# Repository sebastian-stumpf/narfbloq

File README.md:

# narfbloq

A wireless version of the narfpad.

## BOM

- narfpad PCB
- 1 Seeed Studio XIAO nRF52840
- 10 SOD123 diodes
- 9 Kailh Choc Hotswap Sockets
- 9 Choc Switches (and keycaps)
- 1 EC11 Encoder
- 1 Reset Button (optional but recommended since the one on the MCU is really tiny)
- 1 MSK-12C02 Switch
- 1 JST-PH 2mm connector
- 1 3.7V LiPo battery with JST-PH 2mm connector (I designed this for a 30x40x6.5 battery which fits the case nicely)
- 1 3D printed case (I scaled it to 102% and the PCB fits it quite nicely at that size)

## Firmware

Firmware available here:

https://github.com/sebastian-stumpf/zmk-config-narfbloq

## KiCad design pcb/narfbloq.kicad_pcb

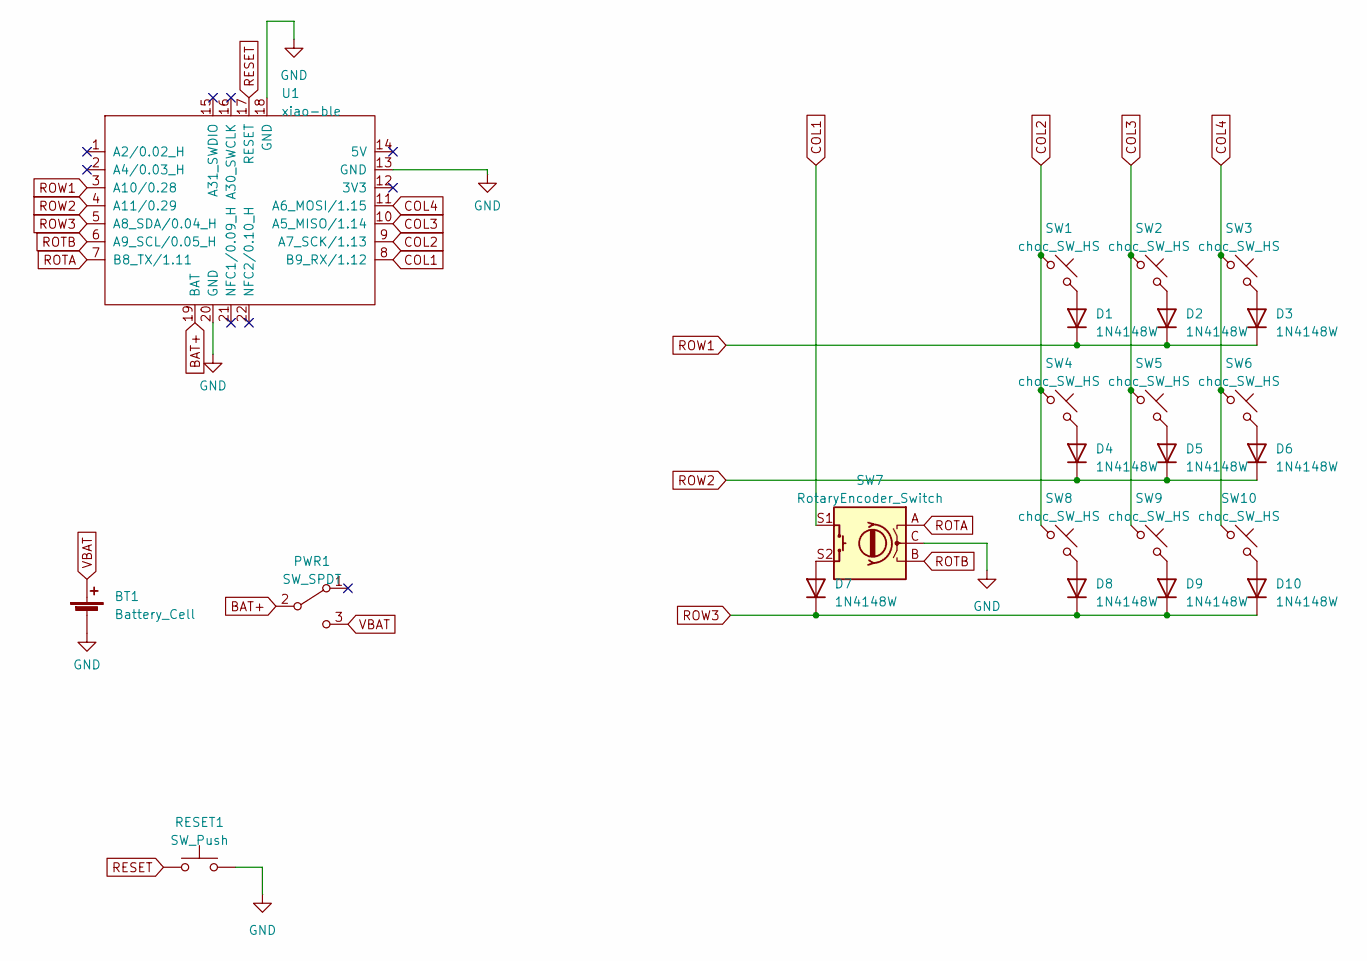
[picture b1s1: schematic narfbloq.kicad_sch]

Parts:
BT1: Battery_Cell; JST_PH_S2B-PH-K_1x02_P2.00mm_Horizontal
D1, D2, D3, D4, D5, D6, D7, D8, D9, D10: 1N4148W; D_SOD-123
PWR1: SW_SPDT; switch-MSK-12C02-smd
RESET1: SW_Push; ResetSW
SW1, SW2, SW3, SW4, SW5, SW6, SW8, SW9, SW10: choc_SW_HS; SW_choc_HS_1u
SW7: RotaryEncoder_Switch; RotaryEncoder_EC11
U1: xiao-ble; xiao-ble-tht

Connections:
BAT+: PWR1.2 (B), U1.19 (BAT)
COL1: SW7.S1, U1.8 (B9_RX/1.12)
COL2: SW1.1, SW4.1, SW8.1, U1.9 (A7_SCK/1.13)
COL3: SW2.1, SW5.1, SW9.1, U1.10 (A5_MISO/1.14)
COL4: SW3.1, SW6.1, SW10.1, U1.11 (A6_MOSI/1.15)
GND: BT1.2 (-), RESET1.2, SW7.C, U1.13 (GND), U1.18 (GND), U1.20 (GND)
unnamed: D1.2 (A), SW1.2
unnamed: D2.2 (A), SW2.2
unnamed: D3.2 (A), SW3.2
unnamed: D4.2 (A), SW4.2
unnamed: D5.2 (A), SW5.2
unnamed: D6.2 (A), SW6.2
unnamed: D7.2 (A), SW7.S2
unnamed: D8.2 (A), SW8.2
unnamed: D9.2 (A), SW9.2
unnamed: D10.2 (A), SW10.2
RESET: RESET1.1, U1.17 (RESET)
ROTA: SW7.A, U1.7 (B8_TX/1.11)
ROTB: SW7.B, U1.6 (A9_SCL/0.05_H)
ROW1: D1.1 (K), D2.1 (K), D3.1 (K), U1.3 (A10/0.28)
ROW2: D4.1 (K), D5.1 (K), D6.1 (K), U1.4 (A11/0.29)
ROW3: D7.1 (K), D8.1 (K), D9.1 (K), D10.1 (K), U1.5 (A8_SDA/0.04_H)
VBAT: BT1.1 (+), PWR1.3 (C)

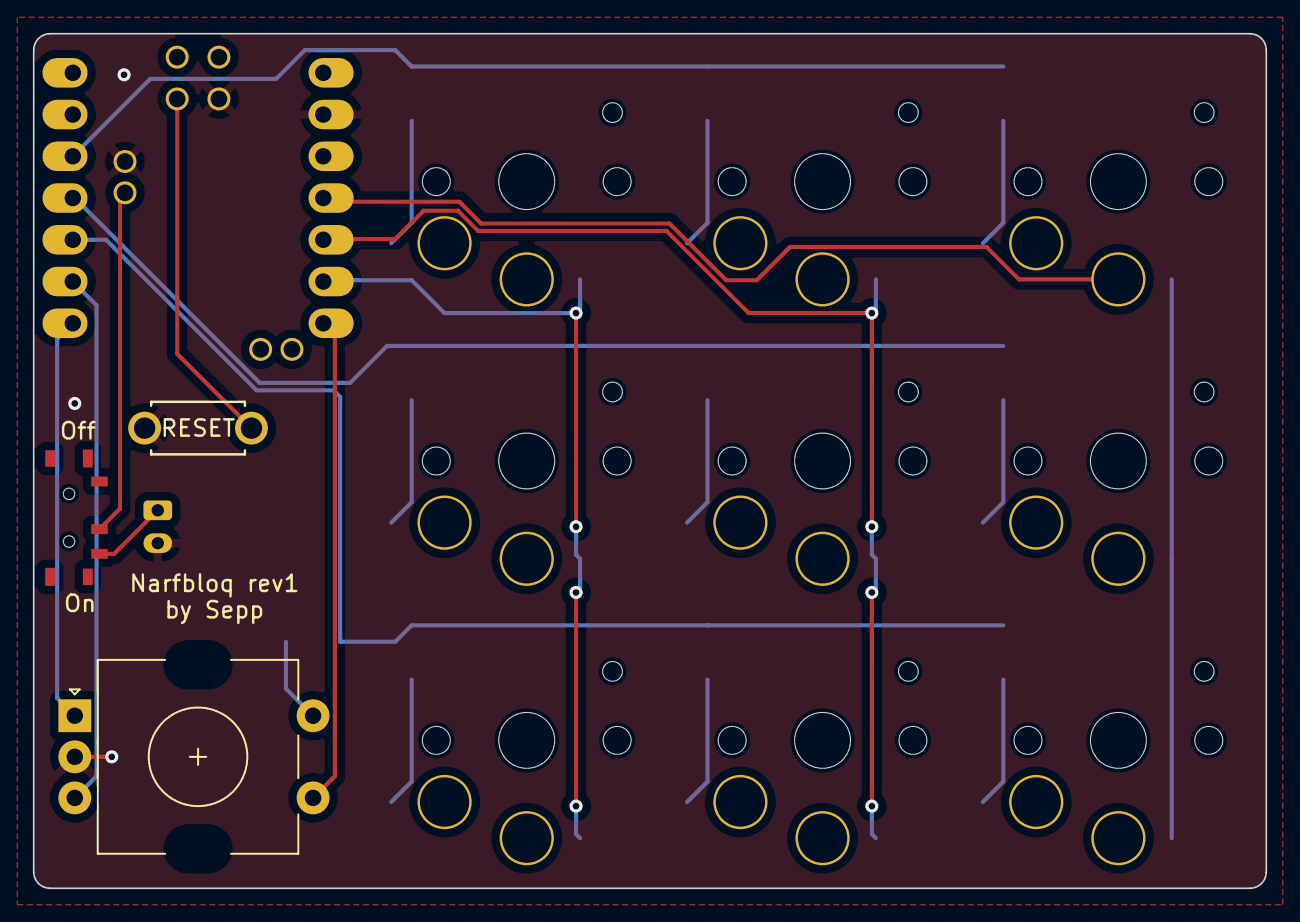
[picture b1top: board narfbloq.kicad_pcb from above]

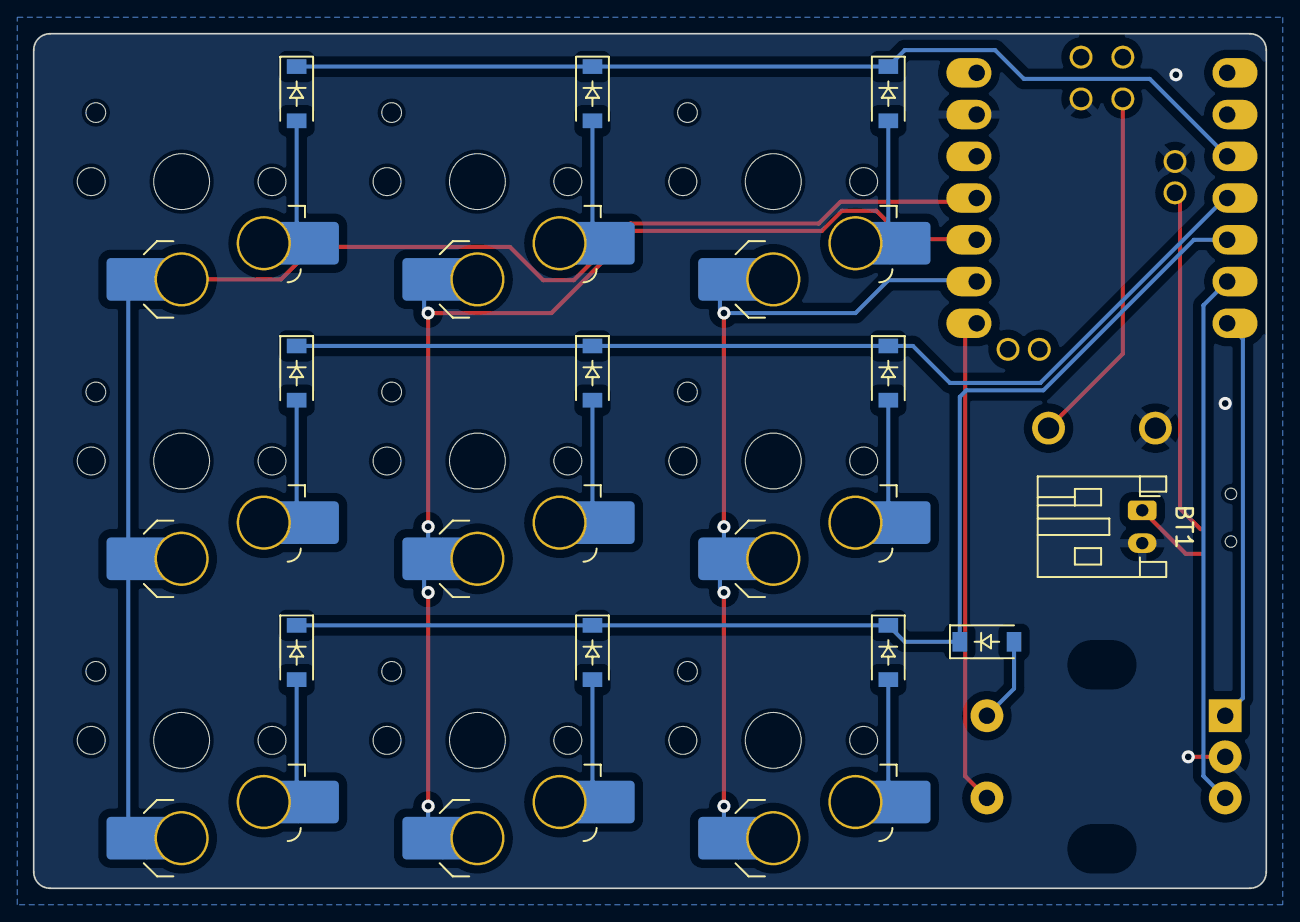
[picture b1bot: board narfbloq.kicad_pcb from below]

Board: 2 copper layers, 75.0 x 52.0 mm, 24 parts (11 on the bottom side), 23 nets.

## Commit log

2023-03-29 changed filename
